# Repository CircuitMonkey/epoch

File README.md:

# Epoch 1
A 16 channel hand-held vibrator controller (haptic field emitter). With LCD Touch Screen and SD Card reader. Replaced by [Epoch-2](https://github.com/CircuitMonkey/epoch-2)

## Features
 - TFT Touch Display - 320x240 - 3.2inch - SPI Type - Resistive Touch
 - Adafruit Huzzah32 ESP Controller Board (#3405)
 - TLC59401RHB SPI PWM Channel Driver
 - LiPo Battery - 62mm x 50mm, 2500mAH, Adafruit (#328)
 - Molex MiniFitJr type connectors with custom cables.
 - Programmed in Arduino
 - Approximate size of original Apple iPod.

## Dev Notes
 - Huzzah has on-board LiPo charger which made integration simple.
 - Choice of Molex MinifitJr type connectors was cumbersome in use.
 - Choice of Molex MinifitJr type connectors made custom cable fabrication time consuming.
 - This platform performed well for almost a year, before Epoch-2 developed.
 - Never used SD card. Removed off future designs.
 - Choice of TLC59401RHB was cumbersome in coding. Moved to I2C type PWM chip in future Epoch designs.
 - Choice of TLC59401RHB limited motor size as only could source 120mA per channel. Added power FETs to future Epoch designs.

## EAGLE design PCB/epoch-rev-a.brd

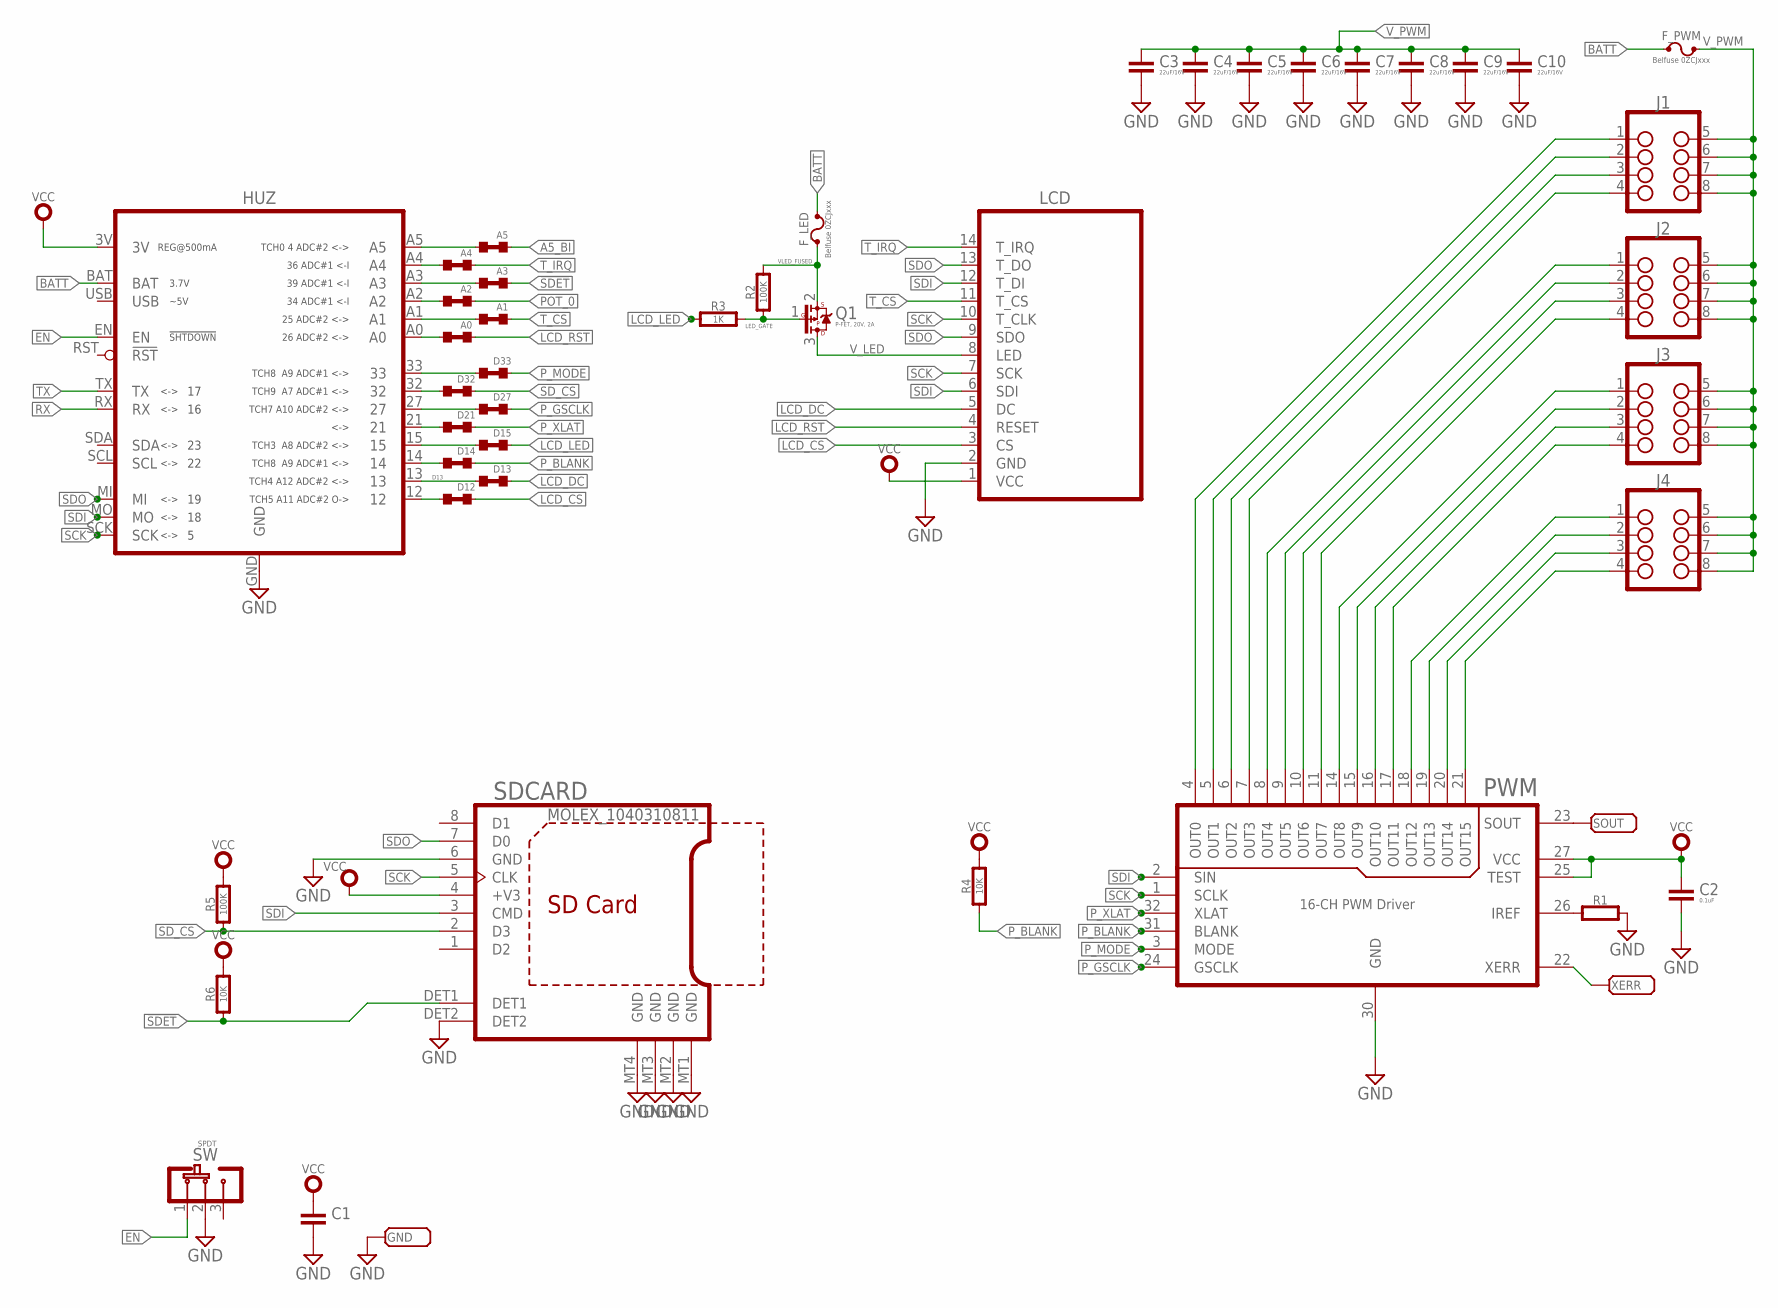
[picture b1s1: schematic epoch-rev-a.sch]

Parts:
A0, A1, A2, A3, A4, A5: NP; 0603-SHORT
C1: CAPACITOR0603; 0603-CAP
C2: 0.1uF; 0603-CAP
C3, C4, C5, C6, C7, C8, C9, C10: 22uF/16V; 1210-CAP
D12, D13, D14, D15, D21, D27, D32, D33: NP; 0603-SHORT
F_LED: Belfuse 0ZCJxxx; BELFUSE-1206
F_PWM: Belfuse 0ZCJxxx; BELFUSE-1206
GND: PADSMD-050X050; SMD-050X050
HUZ: HUZZAHHUZZAH; ADAFRUIT_HUZZAH32
J1, J2, J3, J4: NANOFIT-08P-DR-RA-THD; MOLEX-105314-XX08
LCD: LCD-320X240-3.2-INCH-SPI-DIANN-LOWPROFILE; LCD-320X240-DIANN-3.2-LP-SOCKET
PWM: 16-CH PWM Driver; QFN-32
Q1: P-FET, 20V, 2A; SOT-23
R1: RESISTOR0603; 0603-RES
R2, R5: 100K; 0603-RES
R3: 1K; 0603-RES
R4, R6: 10K; 0603-RES
SDCARD: MOLEX_1040310811; MOLEX_1040310811_USD
SOUT: PADSMD-050X050; SMD-050X050
SW: SPDT; CK_TS01C
XERR: PADSMD-050X050; SMD-050X050

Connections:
!SDET: A3.4 (2), R6.1, SDCARD.DET1
A5_BI: A5.4 (2)
BATT: F_LED.2, F_PWM.1, HUZ.BAT
D12: D12.3 (1), HUZ.12
D13: D13.3 (1), HUZ.13
D14: D14.3 (1), HUZ.14
D15: D15.3 (1), HUZ.15
EN: HUZ.EN, SW.1 (A)
GND: C1.2, C2.2, C3.2, C4.2, C5.2, C6.2, C7.2, C8.2, C9.2, C10.2, GND.1, HUZ.GND, LCD.2 (GND), PWM.30 (GND), R1.2, SDCARD.6 (GND), SDCARD.DET2, SDCARD.MT1 (GND), SDCARD.MT2 (GND), SDCARD.MT3 (GND), SDCARD.MT4 (GND), SW.2 (C)
LCD_CS: D12.4 (2), LCD.3 (CS)
LCD_DC: D13.4 (2), LCD.5 (DC)
LCD_LED: D15.4 (2), R3.1
LCD_RST: A0.4 (2), LCD.4 (RESET)
LED_GATE: Q1.1 (G), R2.1, R3.2
unnamed: J4.4, PWM.21 (OUT15)
unnamed: J4.3, PWM.20 (OUT14)
unnamed: J4.2, PWM.19 (OUT13)
unnamed: J4.1, PWM.18 (OUT12)
unnamed: J3.4, PWM.17 (OUT11)
unnamed: J3.3, PWM.16 (OUT10)
unnamed: J3.2, PWM.15 (OUT9)
unnamed: J3.1, PWM.14 (OUT8)
unnamed: J2.4, PWM.11 (OUT7)
unnamed: J2.3, PWM.10 (OUT6)
unnamed: J2.2, PWM.9 (OUT5)
unnamed: J2.1, PWM.8 (OUT4)
unnamed: J1.4, PWM.7 (OUT3)
unnamed: J1.3, PWM.6 (OUT2)
unnamed: J1.2, PWM.5 (OUT1)
unnamed: J1.1, PWM.4 (OUT0)
unnamed: PWM.26 (IREF), R1.1
unnamed: PWM.22 (XERR), XERR.1
unnamed: PWM.23 (SOUT), SOUT.1
unnamed: D21.3 (1), HUZ.21
unnamed: D27.3 (1), HUZ.27
unnamed: D32.3 (1), HUZ.32
unnamed: D33.3 (1), HUZ.33
unnamed: A0.3 (1), HUZ.A0
unnamed: A1.3 (1), HUZ.A1
unnamed: A2.3 (1), HUZ.A2
unnamed: A3.3 (1), HUZ.A3
unnamed: A4.3 (1), HUZ.A4
unnamed: A5.3 (1), HUZ.A5
POT_0: A2.4 (2)
P_BLANK: D14.4 (2), PWM.31 (BLANK), R4.1
P_GSCLK: D27.4 (2), PWM.24 (GSCLK)
P_MODE: D33.4 (2), PWM.3 (MODE)
P_XLAT: D21.4 (2), PWM.32 (XLAT)
RX: HUZ.RX
SCK: HUZ.SCK, LCD.7 (SCK), LCD.10 (T_CLK), PWM.1 (SCLK), SDCARD.5 (CLK)
SDI: HUZ.MO, LCD.6 (SDI), LCD.12 (T_DI), PWM.2 (SIN), SDCARD.3 (CMD)
SDO: HUZ.MI, LCD.9 (SDO), LCD.13 (T_DO), SDCARD.7 (D0)
SD_CS: D32.4 (2), R5.1, SDCARD.2 (D3)
TX: HUZ.TX
T_CS: A1.4 (2), LCD.11 (T_CS)
T_IRQ: A4.4 (2), LCD.14 (T_IRQ)
VCC: C1.1, C2.1, HUZ.3V, LCD.1 (VCC), PWM.25 (TEST), PWM.27 (VCC), R4.2, R5.2, R6.2, SDCARD.4 (+V3)
VLED_FUSED: F_LED.1, Q1.2 (S), R2.2
V_LED: LCD.8 (LED), Q1.3 (D)
V_PWM: C3.1, C4.1, C5.1, C6.1, C7.1, C8.1, C9.1, C10.1, F_PWM.2, J1.5, J1.6, J1.7, J1.8, J2.5, J2.6, J2.7, J2.8, J3.5, J3.6, J3.7, J3.8, J4.5, J4.6, J4.7, J4.8

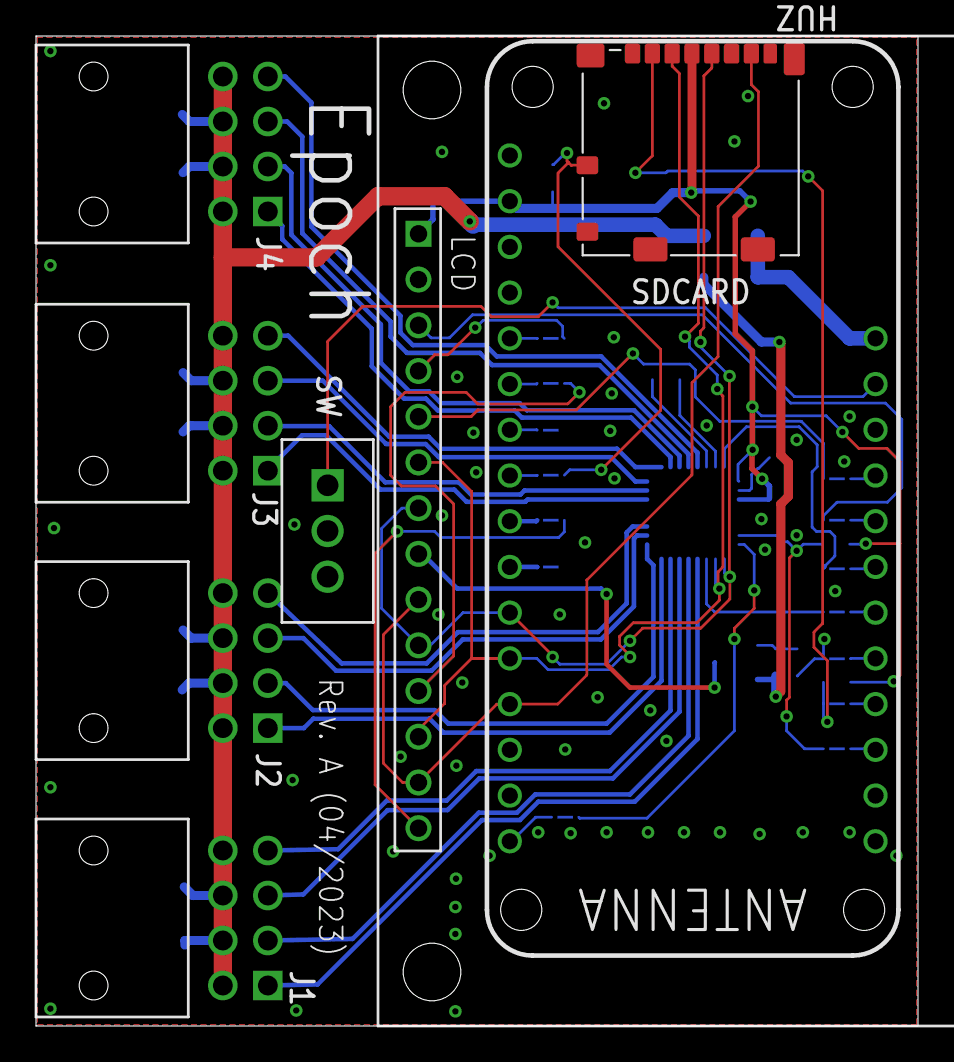
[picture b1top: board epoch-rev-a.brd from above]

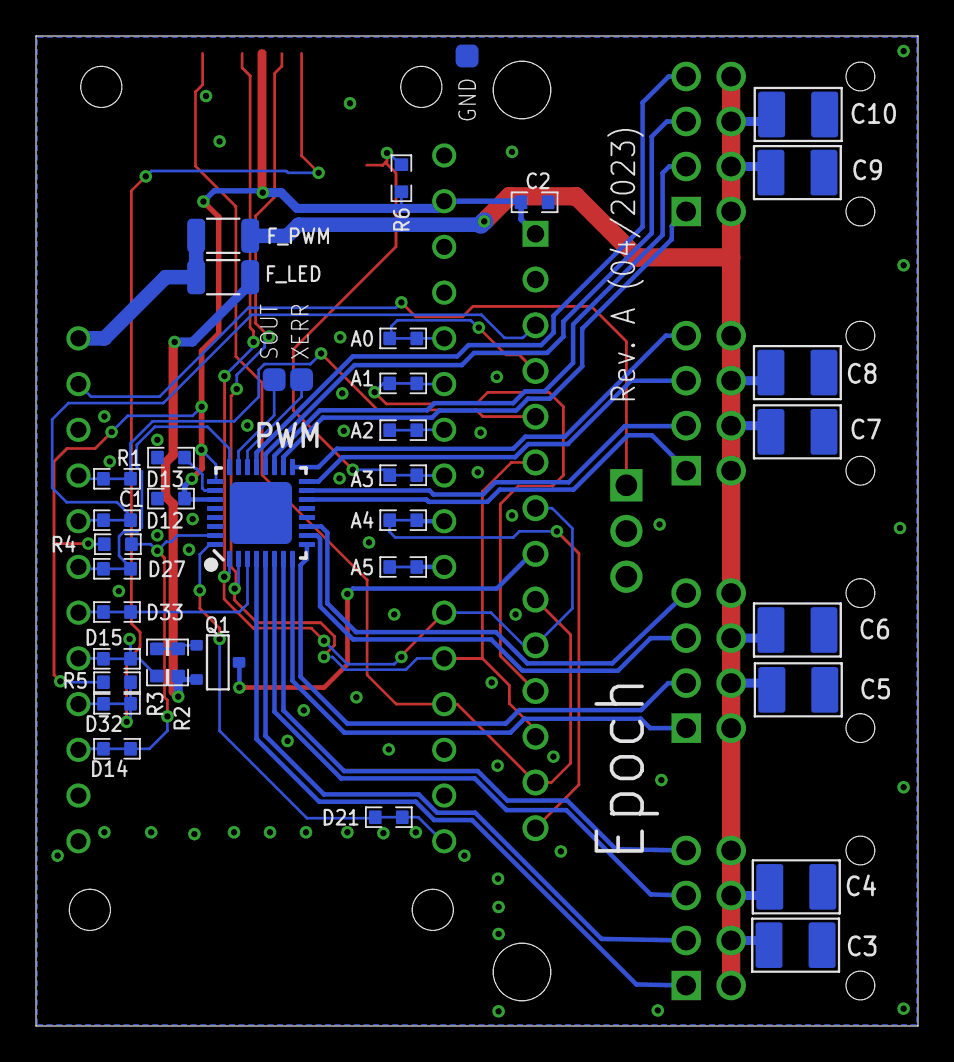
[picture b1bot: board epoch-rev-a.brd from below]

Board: 2 copper layers, 49.0 x 55.0 mm, 45 parts (37 on the bottom side), 56 nets.

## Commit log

2023-04-21 Add Rev A of Epoch
2023-04-22 Added BOM and placement docs.
2023-11-18 Added Diagram
2024-01-03 Basic UI proof of concept.
2024-01-03 Bill of Materials
2024-01-04 Allow slider disable.
2024-01-04 Allow range max limit on slider for values less than 255.
2024-01-08 Create tests for motor chip
2024-01-09 Was transferring wrong length in GS register
2024-01-09 Get rid of old print statements.
2024-01-09 Integrated motor chip TLC59401
2024-01-09 Clean up unused code.
2024-01-09 add print TFT settings util
2024-01-10 Add set with weighted curve.
2024-01-10 Clean up code and comments.
2024-01-10 UI template for 4 sliders built into UI.cpp
2024-01-10 Add UI Style disc template.
2024-01-10 shift Back glyph to the right a few pixels.
2024-01-10 Clean up mode 1 code.
2024-01-10 Add mode 2 (dual motor pairs)
2024-01-10 Remove unused case statements.
2024-01-12 Cycle working for two and four motors.
2024-01-24 Fix cut-paste typos.
2024-01-24 Add Mode 8. Full ride.
2024-01-27 WIP. Plunge and Draw need work.
2024-02-01 Create Mode4(for testing) and enhance Mode 8
2025-04-02 Update glyphs.h
    Newer arduino C++ uses modern binary number reference "0b01010101"
2025-04-02 Update epoch-fw.ino
    Espresif changed how timers are used. Add hook for mode 7.
2025-04-02 Add mode 7
2025-04-02 Change GS clock settings.
2025-04-02 Update tlc59401.cpp
    Newer Espresif changed how led control works.
2025-04-28 Add images of Epoch 1 unit.
2025-04-28 Fix typo in pathname for images.
2026-02-21 Add images. Update Readme.
